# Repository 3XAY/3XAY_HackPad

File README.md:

# HackPad

This is currently a work in progress. **THIS MEANS NOTHING IS TESTED, DO NOT ATTEMPT TO USE THIS AS A GUIDE** (as of now)
[here's the submission link if you want it](https://github.com/hackclub/hackpad/pull/187)

This is my submission for Hack Club's HackPad YSWS (You ship we ship).
My progress will be throughouly documented here.

## Images
These are screenshots from the development process with each design iteration. (For the PCB / Case, code can be reviewed via the version history)

## KiCad
These are the KiCad files.

## Blender
Any Blender files made will be stored here, these are either sketches, renders, or CAD files
- Here's the tool I used to export from KiCad to Blender: https://github.com/30350n/pcb2blender

## Firmware
All of the firmware is written in Circuitpython (currently untested)

## YouTube Shorts Recaps
https://youtube.com/playlist?list=PL8pZ9v0F1Ks2gfHrP7J-pUTj4NAnL8gHc&si=MliIfDuidp5TVAae

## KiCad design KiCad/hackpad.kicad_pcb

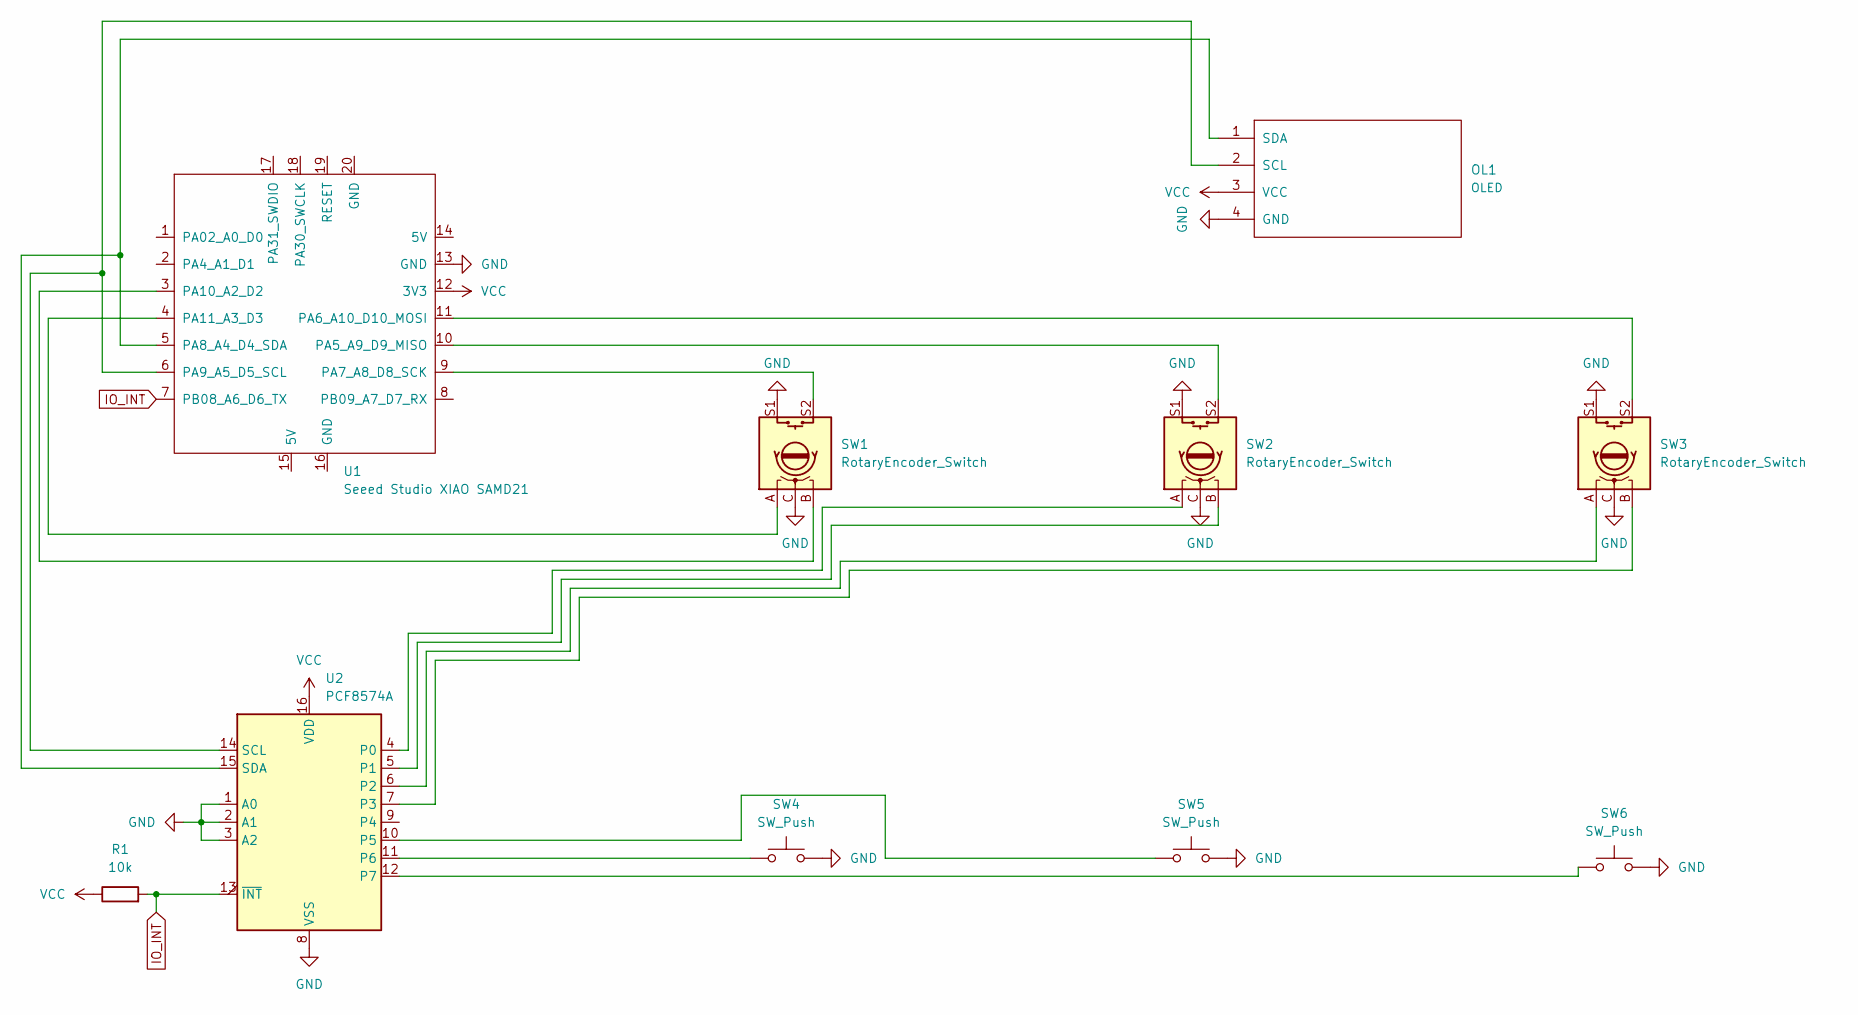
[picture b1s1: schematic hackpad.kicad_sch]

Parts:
OL1: OLED
R1: 10k; R_Axial_DIN0207_L6.3mm_D2.5mm_P10.16mm_Horizontal
SW1, SW2, SW3: RotaryEncoder_Switch; RotaryEncoder_Alps_EC11E-Switch_Vertical_H20mm
SW4, SW5, SW6: SW_Push; SW_Cherry_MX_1.00u_PCB
U1: Seeed Studio XIAO SAMD21; XIAO-Generic-Thruhole-14P-2.54-21X17.8MM
U2: PCF8574A; DIP-16_W7.62mm

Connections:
GND: OL1.4 (GND), SW1.C, SW1.S1, SW2.C, SW2.S1, SW3.C, SW3.S1, SW4.2, SW5.2, SW6.2, U1.13 (GND), U2.1 (A0), U2.2 (A1), U2.3 (A2), U2.8 (VSS)
IO_INT: R1.2, U1.7 (PB08_A6_D6_TX), U2.13 (~INT)
unnamed: OL1.2 (SCL), U1.6 (PA9_A5_D5_SCL), U2.14 (SCL)
unnamed: OL1.1 (SDA), U1.5 (PA8_A4_D4_SDA), U2.15 (SDA)
unnamed: SW2.S2, U1.10 (PA5_A9_D9_MISO)
unnamed: SW3.S2, U1.11 (PA6_A10_D10_MOSI)
unnamed: SW1.S2, U1.9 (PA7_A8_D8_SCK)
unnamed: SW1.B, U1.3 (PA10_A2_D2)
unnamed: SW1.A, U1.4 (PA11_A3_D3)
unnamed: SW2.A, U2.4 (P0)
unnamed: SW2.B, U2.5 (P1)
unnamed: SW3.A, U2.6 (P2)
unnamed: SW3.B, U2.7 (P3)
unnamed: SW5.1, U2.10 (P5)
unnamed: SW4.1, U2.11 (P6)
unnamed: SW6.1, U2.12 (P7)
VCC: OL1.3 (VCC), R1.1, U1.12 (3V3), U2.16 (VDD)

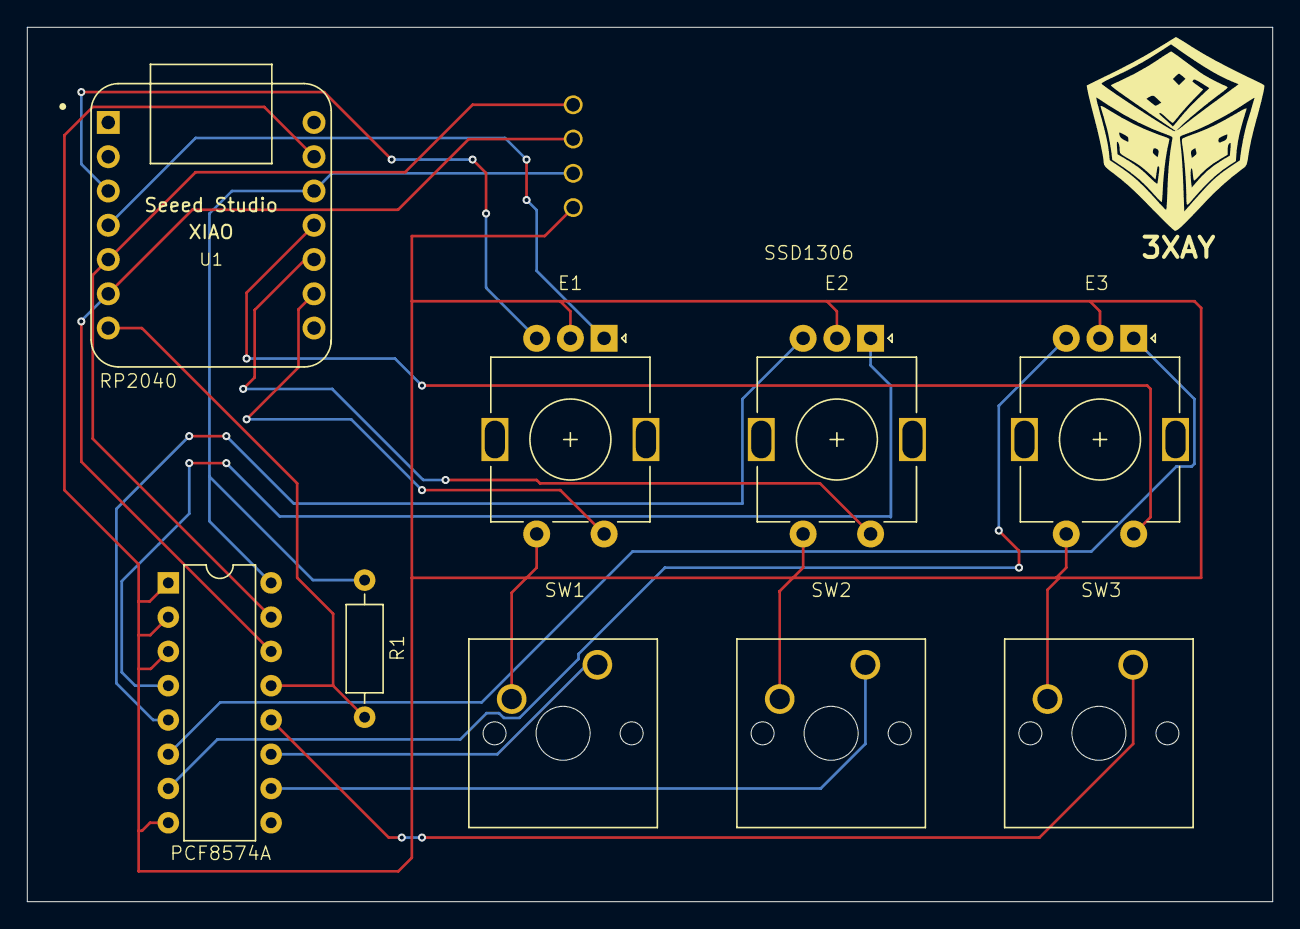
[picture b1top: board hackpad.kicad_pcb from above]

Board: 2 copper layers, 92.3 x 64.8 mm, 10 parts (0 on the bottom side), 17 nets.

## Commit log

2024-10-10 Upload screenshots
2024-10-10 Create Images and V1 folder
2024-10-10 Make V3 folder and place idea.png
2024-10-10 Rename BlenderKeymap.jpg to Images/V3/BlenderKeymap.jpg
2024-10-10 Rename DavinciKeymap.jpg to Images/V3/DavinciKeymap.jpg
2024-10-10 Rename unfinishedPCB.png to Images/V3/unfinishedPCB.png
2024-10-10 Rename finishedSchematic.png to Images/V3/finishedSchematic.png
2024-10-10 Rename actuallyFinished.png to Images/V2/actuallyFinished.png
2024-10-10 Rename finished(OrSoIThought)Schematic.png to Images/V2/finished(OrSoIThought)Schematic.png
2024-10-10 Rename finishedButIMessedUpSchematic.png to Images/V2/finishedButIMessedUpSchematic.png
2024-10-10 Rename footprintAssignments.png to Images/V2/footprintAssignments.png
2024-10-10 Rename unfinishedSchematic.png to Images/V2/unfinishedSchematic.png
2024-10-10 Upload idea.png for V2
2024-10-10 Upload KiCad Files
2024-10-10 Rename hackpad.kicad_prl to KiCad/hackpad.kicad_prl
2024-10-10 Rename hackpad.kicad_pro to KiCad/hackpad.kicad_pro
2024-10-10 Added blend files
2024-10-10 Rename hackpadIdea.blend to Blender/hackpadIdea_V3.blend
2024-10-11 Delete Images/V3/idea.png
    File was empty
2024-10-11 HackPad Day 4 Images
2024-10-11 HackPad Day 4 KiCad Files
2024-10-11 Fixed YouTube Shorts header
2024-10-11 Kbd files
2024-10-11 Remaining KiCad libraries
2024-10-11 Delete KiCad/footprints/empty.txt
    This was only used to make the "footprints" folder
2024-10-11 More pictures
2024-10-11 Models by PonderSlime
2024-10-11 PCB images with models provided by PonderSlime
2024-10-13 Updated Blender files
2024-10-13 Rename PCBBackMaterial.png to Blender/PCBBackMaterial.png
2024-10-13 Rename hackpadCAD.blend to Blender/hackpadCAD.blend
2024-10-13 Rename PCBFrontMaterial.png to Blender/PCBFrontMaterial.png
2024-10-14 Add PCB V3.5 Images
2024-10-14 PCB V3.5 KiCad Files Update
2024-10-14 Official HackPad OLED Footprint (PCB V3.5)
2024-10-14 PCB V3.5 to Blender file (PCB2Blender output)
2024-10-15 Added unfinished case CAD images (V3.5)
2024-10-15 Update CAD (V3.5)
2024-10-17 Upload case (V3.5) files in OBJ and 3MF
2024-10-17 Add finished case (V3.5) images from top and USB
2024-10-17 Upload finished blend file for case (V3.5)
2024-10-17 Started QMK process
2024-10-17 Update readme.md (for QMK firmware)
    Cleared the pre-made info
2024-10-18 Restart QMK and I have no clue what's going on
2024-10-18 Delete QMK directory
    I actually hate qmk bruh
2024-10-20 Finished firmware (V0.1)
    This firmware should have basic functionality for Davinci Resolve
    There are also some files for the codeWithCustomLibs.py file, this is a test. It is not designed to be ran.
2024-10-20 Fixed errors
    - Acrylic switch plate now has 3mm holes, but 3d printed parts still have 2.9mm
    - Made top plate 1mm taller to accommodate 20mm M3 screws
    - Flattened the switch plate (was slightly curved before, which would be HORRIBLE for CNCing the plate)
2024-10-20 Fixed errors
    - Reuploaded exported files with errors fixed
    - Read the rules and also uploaded all of the parts in one file for each format
2024-10-21 Added rendered pics of macropad
2024-10-21 Fixed switch plate errors
    Resistor hole was plugged
    Key switch holes were too loose
2024-10-21 Re-upload fixed CAD files
    - Fixed resistor hole being plugged
    - Fixed switch plate hole sizing
